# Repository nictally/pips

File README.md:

PIPS is a perimeter intrusion protection system

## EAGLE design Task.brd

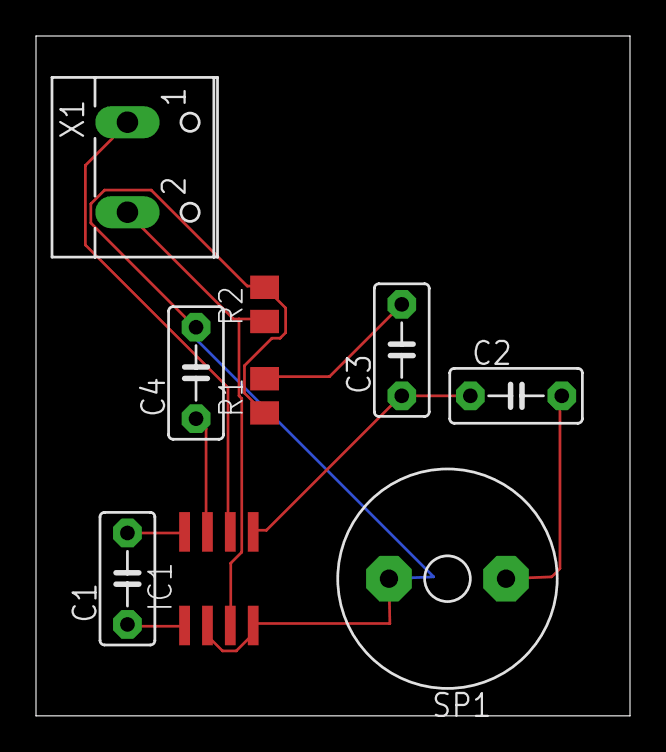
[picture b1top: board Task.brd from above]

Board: 2 copper layers, 33.0 x 37.8 mm, 9 parts (0 on the bottom side), 9 nets.

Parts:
C1: 10 uF; C5B3
C2: 250 uF; C5B3
C3: 0.05 uF; C5B3
C4: C5B3
IC1: LM386M-1; SO08
R1: 10; M0805
R2: 10 k; M0805
SP1: AL60P
X1: W237-102

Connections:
GND: C4.2, IC1.2, IC1.4, R1.1, R2.2, SP1.2
unnamed: C4.1, IC1.7
unnamed: C1.1, IC1.1
unnamed: C1.2, IC1.8
unnamed: C2.1, C3.1, IC1.5
unnamed: C3.2, R1.2
unnamed: C2.2, SP1.1
unnamed: IC1.6, X1.1
unnamed: IC1.3, R2.1, X1.2

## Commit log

2017-05-30 this is toms task
2017-05-30 updated folders
2017-05-30 Added Task.sch
2017-05-31 add concrete1 file
2017-06-01 adding all designs and components
